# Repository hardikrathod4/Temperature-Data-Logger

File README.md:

# TEMPERATURE DATA LOGGER
8 channel K-type thermocouple temperature logger.

## FEATURES
* ESP32-WROOM-32E as a Controller
* 8 channel K-type thermocouple inputs (MAX31855KASA)
* 20x4 char LCD display
* MicroSD memory card interface
* Buzzer
* Power and data in/out over USB type-B connector
* RTC (PCF8563T)
* 4 buttons for menu
* 3 LEDs for status indication

## STATUS
### Hardware
- [X] In progress
- [ ] Completed
### Functional Testing (HW+SW)
- [ ] Programming
- [ ] Serial data over USB-B (Serial2)
- [ ] Menu Buttons check
- [ ] LEDs check
- [ ] RTC check
- [ ] LCD check
- [ ] Buzzer check
- [ ] microSD check
- [ ] Thermocouple temperature read check
- [ ] is somthing missing???
### Software
- [ ] TBD
### Enclosure
- [X] In progress
- [ ] Completed

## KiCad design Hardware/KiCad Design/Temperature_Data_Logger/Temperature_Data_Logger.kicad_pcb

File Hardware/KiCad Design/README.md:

# NOTE
It isn't recommended to use older version of the project.

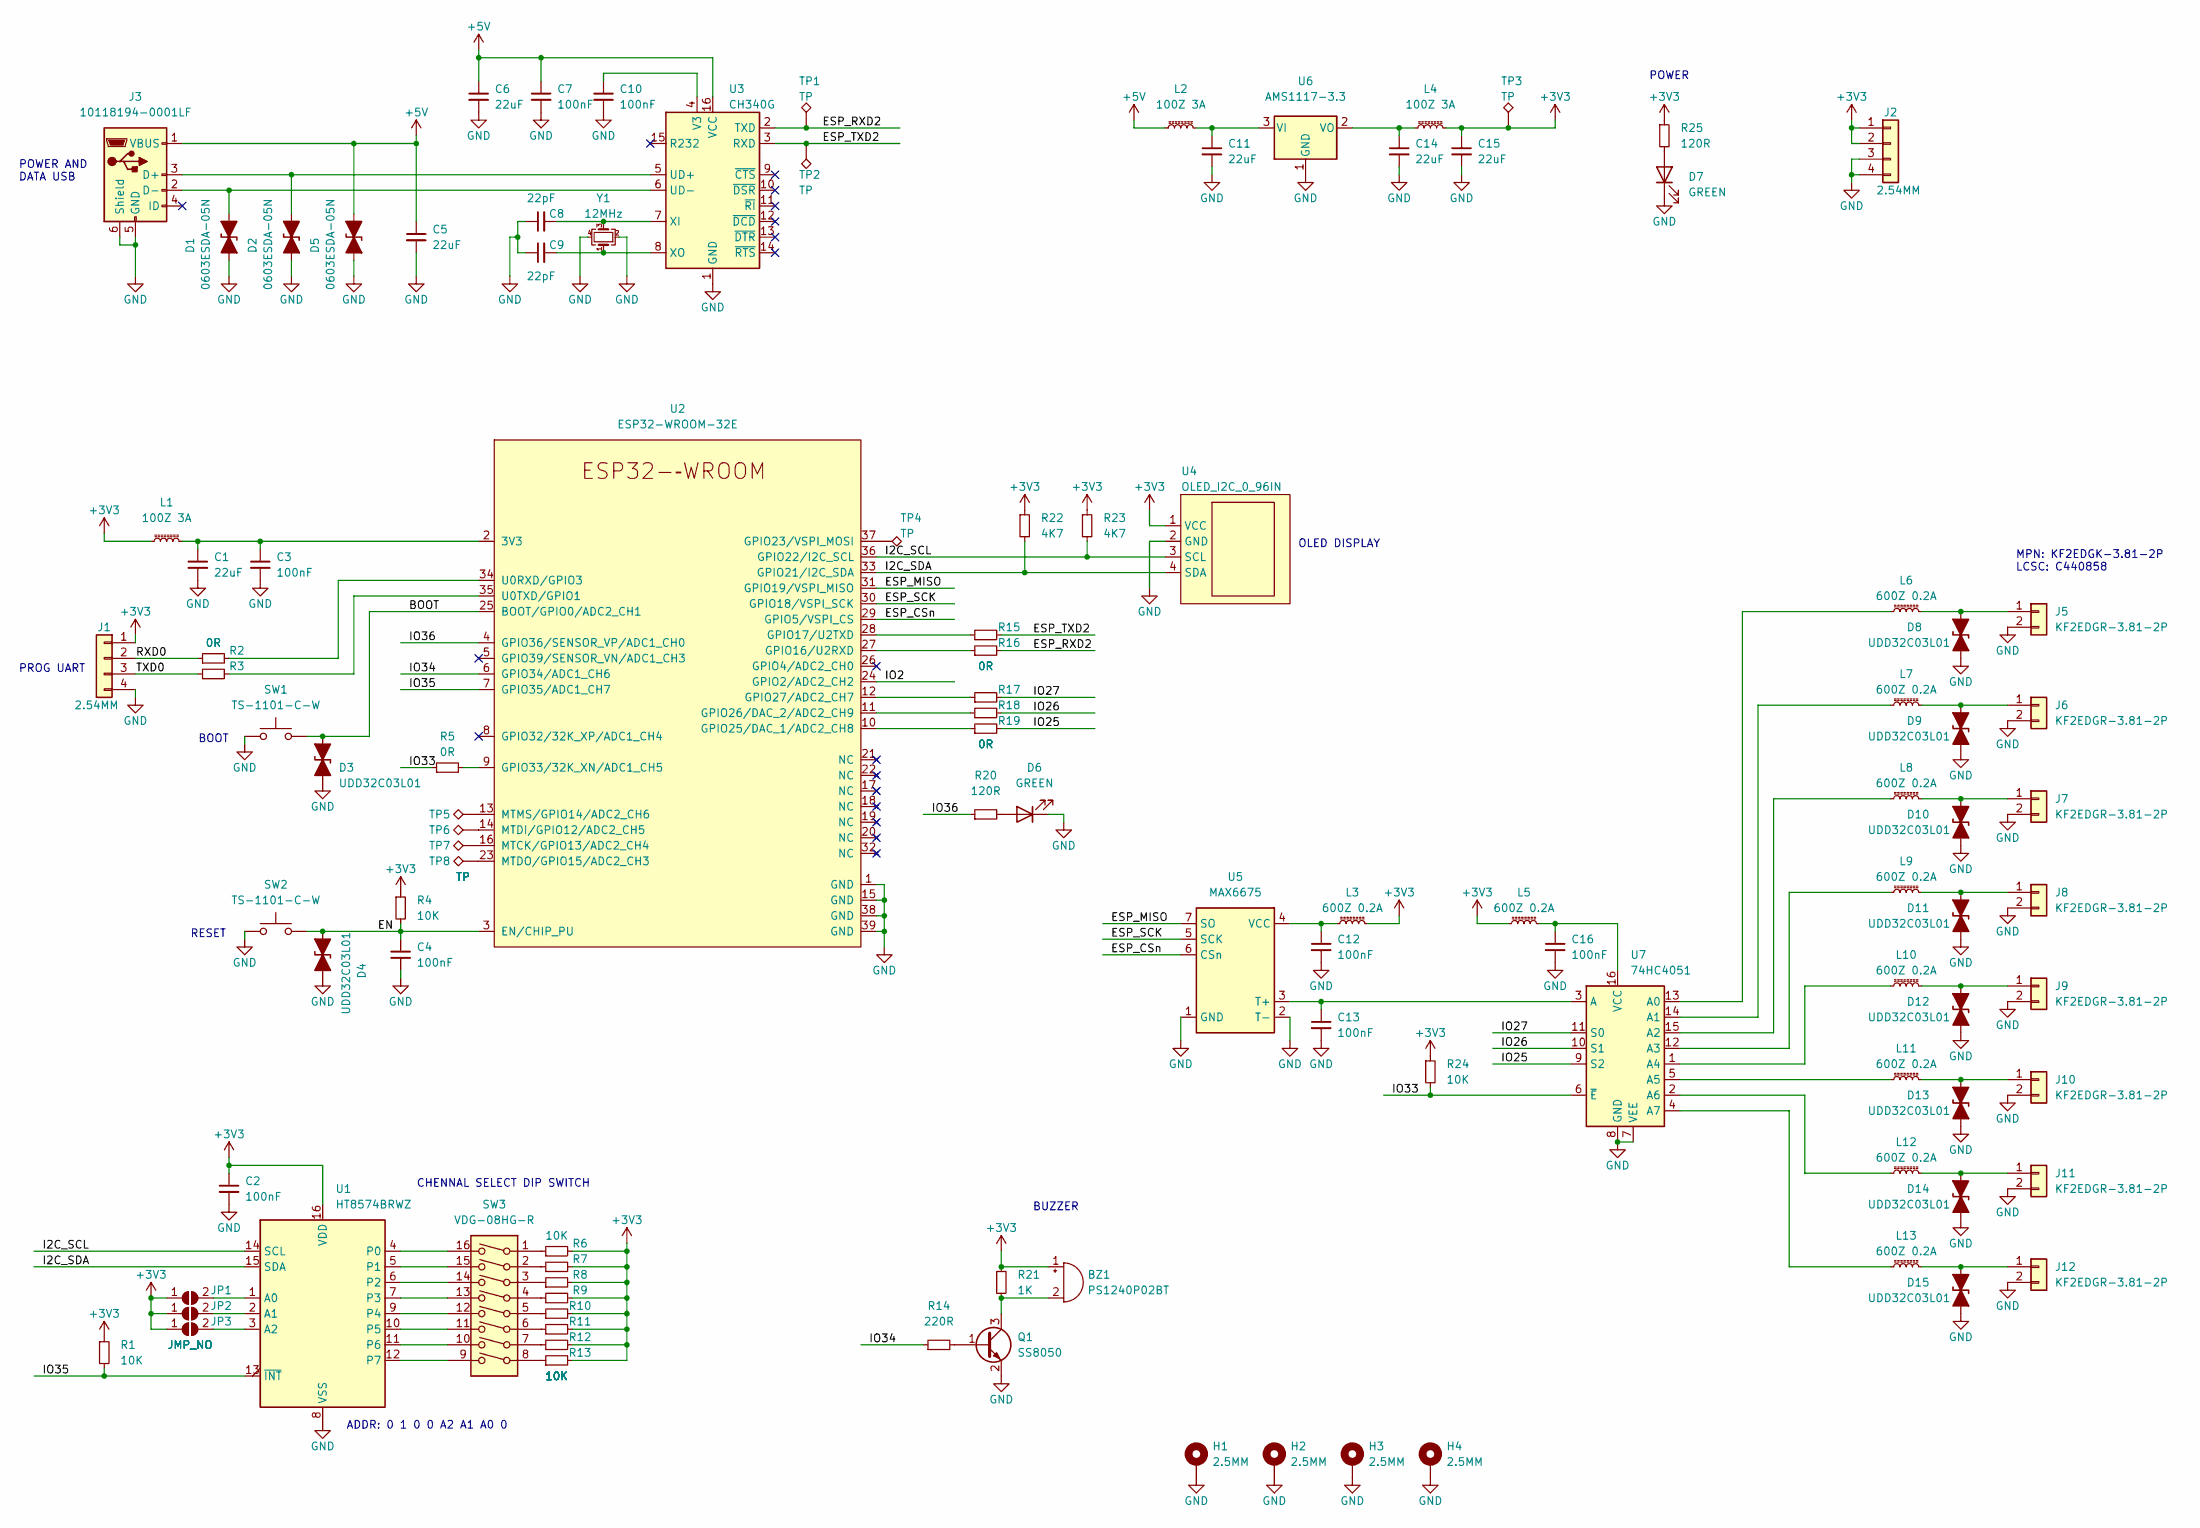
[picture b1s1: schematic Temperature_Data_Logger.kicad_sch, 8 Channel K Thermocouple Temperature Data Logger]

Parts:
BZ1: PS1240P02BT; Buzzer_TDK_PS1240P02BT_D12.2mm_H6.5mm; LCSC C76871
C1, C5, C6, C11, C14, C15: 22uF; C_0603_1608Metric; LCSC C59461
C2, C3, C4, C7, C10, C12, C13, C16: 100nF; C_0603_1608Metric; LCSC C14663
C8, C9: 22pF; C_0603_1608Metric; LCSC C1653
D1, D2, D5: 0603ESDA-05N; D_0603_1608Metric; LCSC C316054
D3, D4, D8, D9, D10, D11, D12, D13, D14, D15: UDD32C03L01; D_SOD-323_HandSoldering; LCSC C78439
D6, D7: GREEN; LED_D3.0mm_Clear; LCSC C559113
H1, H2, H3, H4: 2.5MM; MountingHole_2.7mm_M2.5_Pad_Via
J1, J2: 2.54MM; PinHeader_1x04_P2.54mm_Vertical; LCSC C358686
J3: 10118194-0001LF; USB_Micro-B_Amphenol_10118194_Horizontal; LCSC C132563
J5, J6, J7, J8, J9, J10, J11, J12: KF2EDGR-3.81-2P; PhoenixContact_MC_1,5_2-G-3.81_1x02_P3.81mm_Horizontal; LCSC C441182
JP1, JP2, JP3: JMP_NO; SolderJumper-2_P1.3mm_Open_RoundedPad1.0x1.5mm
L1, L2, L4: 100Z 3A; L_0603_1608Metric; LCSC C307769
L3, L5, L6, L7, L8, L9, L10, L11, L12, L13: 600Z 0.2A; L_0603_1608Metric; LCSC C1002
Q1: SS8050; SOT-23; LCSC C2150
R1, R4, R6, R7, R8, R9, R10, R11, R12, R13, R24: 10K; R_0603_1608Metric; LCSC C25804
R2, R3, R5, R15, R16, R17, R18, R19: 0R; R_0603_1608Metric; LCSC C21189
R14: 220R; R_0603_1608Metric; LCSC C22962
R20, R25: 120R; R_0603_1608Metric; LCSC C22787
R21: 1K; R_0603_1608Metric; LCSC C21190
R22, R23: 4K7; R_0603_1608Metric; LCSC C23162
SW1, SW2: TS-1101-C-W; SW_SPST_CK_RS282G05A3; LCSC C318938
SW3: VDG-08HG-R; SW_DIP_SPSTx08_Slide_9.78x22.5mm_W7.62mm_P2.54mm; LCSC C3663
TP1, TP2, TP3, TP4, TP5, TP6, TP7, TP8: TP; TestPoint_Pad_1.0x1.0mm
U1: HT8574BRWZ; SOIC-16W_7.5x10.3mm_P1.27mm; LCSC C2834482
U2: ESP32-WROOM-32E
U3: CH340G; SOIC-16_3.9x9.9mm_P1.27mm; LCSC C14267
U4: OLED_I2C_0_96IN; Display_128x64_096_I2C
U5: MAX6675; SOIC-8_5.23x5.23mm_P1.27mm; LCSC C16030
U6: AMS1117-3.3; SOT-223-3_TabPin2; LCSC C6186
U7: 74HC4051; SOIC-16_3.9x9.9mm_P1.27mm; LCSC C9386
Y1: 12MHz; Crystal_SMD_SeikoEpson_FA238V-4Pin_3.2x2.5mm; LCSC C9002

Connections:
+3V3: BZ1.1 (-), C2.1, C15.1, J1.1, J2.1, J2.2, JP1.1 (A), JP2.1 (A), JP3.1 (A), L1.1, L3.2, L4.2, L5.1, R1.1, R4.1, R6.2, R7.2, R8.2, R9.2, R10.2, R11.2, R12.2, R13.2, R21.1, R22.1, R23.1, R24.1, R25.1, TP3.1, U1.16 (VDD), U4.1 (VCC)
+5V: C5.1, C6.1, C7.1, D5.2 (A2), J3.1 (VBUS), L2.1, U3.16 (VCC)
/BOOT: D3.2 (A2), SW1.2, U2.25 (BOOT/GPIO0/ADC2_CH1)
/EN: C4.1, D4.2 (A2), R4.2, SW2.2, U2.3 (EN/CHIP_PU)
/ESP_CSn: U2.29 (GPIO5/VSPI_CS), U5.6 (CSn)
/ESP_MISO: U2.31 (GPIO19/VSPI_MISO), U5.7 (SO)
/ESP_RXD2: R16.2, TP1.1, U3.2 (TXD)
/ESP_SCK: U2.30 (GPIO18/VSPI_SCK), U5.5 (SCK)
/ESP_TXD2: R15.2, TP2.1, U3.3 (RXD)
/I2C_SCL: R23.2, U1.14 (SCL), U2.36 (GPIO22/I2C_SCL), U4.3 (SCL)
/I2C_SDA: R22.2, U1.15 (SDA), U2.33 (GPIO21/I2C_SDA), U4.4 (SDA)
/IO2: U2.24 (GPIO2/ADC2_CH2)
/IO25: R19.2, U7.9 (S2)
/IO26: R18.2, U7.10 (S1)
/IO27: R17.2, U7.11 (S0)
/IO33: R5.1, R24.2, U7.6 (~E)
/IO34: R14.1, U2.6 (GPIO34/ADC1_CH6)
/IO35: R1.2, U1.13 (~INT), U2.7 (GPIO35/ADC1_CH7)
/IO36: R20.1, U2.4 (GPIO36/SENSOR_VP/ADC1_CH0)
/RXD0: J1.2, R2.1
/TXD0: J1.3, R3.1
GND: C1.2, C2.2, C3.2, C4.2, C5.2, C6.2, C7.2, C8.1, C9.1, C10.2, C11.2, C12.2, C13.2, C14.2, C15.2, C16.2, D1.1 (A1), D2.1 (A1), D3.1 (A1), D4.1 (A1), D5.1 (A1), D6.1 (K), D7.1 (K), D8.1 (A1), D9.1 (A1), D10.1 (A1), D11.1 (A1), D12.1 (A1), D13.1 (A1), D14.1 (A1), D15.1 (A1), H1.1, H2.1, H3.1, H4.1, J1.4, J2.3, J2.4, J3.5 (GND), J3.6 (Shield), J5.2, J6.2, J7.2, J8.2, J9.2, J10.2, J11.2, J12.2, Q1.2 (E), SW1.1, SW2.1, U1.8 (VSS), U2.1 (GND), U2.15 (GND), U2.38 (GND), U2.39 (GND), U3.1 (GND), U4.2 (GND), U5.1 (GND), U5.2 (T-), U6.1 (GND), U7.7 (VEE), U7.8 (GND), Y1.2, Y1.4
unnamed: BZ1.2 (+), Q1.3 (C), R21.2
unnamed: C1.1, C3.1, L1.2, U2.2 (3V3)
unnamed: C8.2, U3.7 (XI), Y1.3
unnamed: C9.2, U3.8 (XO), Y1.1
unnamed: C10.1, U3.4 (V3)
unnamed: C11.1, L2.2, U6.3 (VI)
unnamed: C12.1, L3.1, U5.4 (VCC)
unnamed: C13.1, U5.3 (T+), U7.3 (A)
unnamed: C14.1, L4.1, U6.2 (VO)
unnamed: C16.1, L5.2, U7.16 (VCC)
unnamed: D1.2 (A2), J3.2 (D-), U3.6 (UD-)
unnamed: D2.2 (A2), J3.3 (D+), U3.5 (UD+)
unnamed: D6.2 (A), R20.2
unnamed: D7.2 (A), R25.2
unnamed: D8.2 (A2), J5.1, L6.2
unnamed: D9.2 (A2), J6.1, L7.2
unnamed: D10.2 (A2), J7.1, L8.2
unnamed: D11.2 (A2), J8.1, L9.2
unnamed: D12.2 (A2), J9.1, L10.2
unnamed: D13.2 (A2), J10.1, L11.2
unnamed: D14.2 (A2), J11.1, L12.2
unnamed: D15.2 (A2), J12.1, L13.2
unnamed: JP1.2 (B), U1.1 (A0)
unnamed: JP2.2 (B), U1.2 (A1)
unnamed: JP3.2 (B), U1.3 (A2)
unnamed: L6.1, U7.13 (A0)
unnamed: L7.1, U7.14 (A1)
unnamed: L8.1, U7.15 (A2)
unnamed: L9.1, U7.12 (A3)
unnamed: L10.1, U7.1 (A4)
unnamed: L11.1, U7.5 (A5)
unnamed: L12.1, U7.2 (A6)
unnamed: L13.1, U7.4 (A7)
unnamed: Q1.1 (B), R14.2
unnamed: R2.2, U2.34 (U0RXD/GPIO3)
unnamed: R3.2, U2.35 (U0TXD/GPIO1)
unnamed: R5.2, U2.9 (GPIO33/32K_XN/ADC1_CH5)
unnamed: R6.1, SW3.1
unnamed: R7.1, SW3.2
unnamed: R8.1, SW3.3
unnamed: R9.1, SW3.4
unnamed: R10.1, SW3.5
unnamed: R11.1, SW3.6
unnamed: R12.1, SW3.7
unnamed: R13.1, SW3.8
unnamed: R15.1, U2.28 (GPIO17/U2TXD)
unnamed: R16.1, U2.27 (GPIO16/U2RXD)
unnamed: R17.1, U2.12 (GPIO27/ADC2_CH7)
unnamed: R18.1, U2.11 (GPIO26/DAC_2/ADC2_CH9)
unnamed: R19.1, U2.10 (GPIO25/DAC_1/ADC2_CH8)
unnamed: SW3.9, U1.12 (P7)
unnamed: SW3.10, U1.11 (P6)
unnamed: SW3.11, U1.10 (P5)
unnamed: SW3.12, U1.9 (P4)
unnamed: SW3.13, U1.7 (P3)
unnamed: SW3.14, U1.6 (P2)
unnamed: SW3.15, U1.5 (P1)
unnamed: SW3.16, U1.4 (P0)
unnamed: TP4.1, U2.37 (GPIO23/VSPI_MOSI)
unnamed: TP5.1, U2.13 (MTMS/GPIO14/ADC2_CH6)
unnamed: TP6.1, U2.14 (MTDI/GPIO12/ADC2_CH5)
unnamed: TP7.1, U2.16 (MTCK/GPIO13/ADC2_CH4)
unnamed: TP8.1, U2.23 (MTDO/GPIO15/ADC2_CH3)

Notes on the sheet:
BUZZER
OLED DISPLAY
ADDR: 0 1 0 0 A2 A1 A0 0
CHENNAL SELECT DIP SWITCH
MPN: KF2EDGK-3.81-2P LCSC: C440858
RESET
POWER
POWER AND DATA USB
BOOT
PROG UART

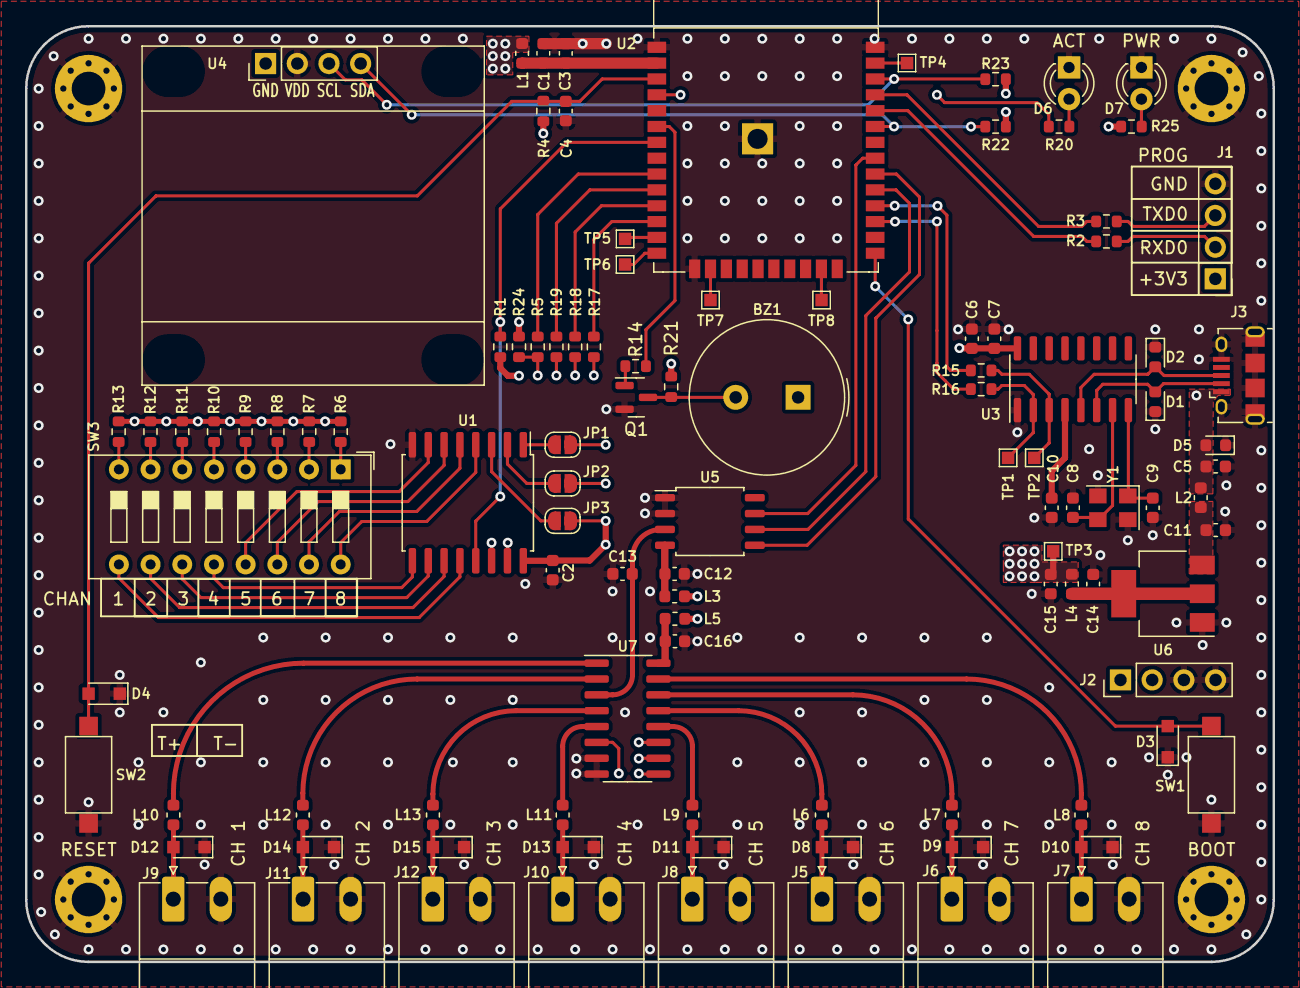
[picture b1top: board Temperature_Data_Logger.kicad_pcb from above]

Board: 4 copper layers, 100.0 x 75.0 mm, 108 parts (0 on the bottom side), 84 nets.

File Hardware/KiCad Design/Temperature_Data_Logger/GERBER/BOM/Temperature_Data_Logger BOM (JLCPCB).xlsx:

Comment | Designator | Footprint | JLCPCB Part
PS1240P02BT | BZ1 | Buzzer_Beeper:Buzzer_TDK_PS1240P02BT_D12.2mm_H6.5mm | C76871
22uF | C1, C5, C6, C11, C14, C15 | Capacitor_SMD:C_0603_1608Metric | C59461
100nF | C2, C3, C4, C7, C10, C12, C13, C16 | Capacitor_SMD:C_0603_1608Metric | C14663
22pF | C8, C9 | Capacitor_SMD:C_0603_1608Metric | C1653
0603ESDA-05N | D1, D2, D5 | Diode_SMD:D_0603_1608Metric | C316054
UDD32C03L01 | D3, D4, D8, D9, D10, D11, D12, D13, D14, D15 | Diode_SMD:D_SOD-323_HandSoldering | C78439
GREEN | D6, D7 | LED_THT:LED_D3.0mm_Clear | C559113
2.5MM | H1, H2, H3, H4 | MountingHole:MountingHole_2.7mm_M2.5_Pad_Via
2.54MM | J1, J2 | Connector_PinHeader_2.54mm:PinHeader_1x04_P2.54mm_Vertical | C358686
10118194-0001LF | J3 | Temperature Data Logger:USB_Micro-B_Amphenol_10118194_Horizontal | C132563
KF2EDGR-3.81-2P | J5, J6, J7, J8, J9, J10, J11, J12 | Connector_Phoenix_MC:PhoenixContact_MC_1,5_2-G-3.81_1x02_P3.81mm_Horizontal | C441182
JMP_NO | JP1, JP2, JP3 | Jumper:SolderJumper-2_P1.3mm_Open_RoundedPad1.0x1.5mm
100Z 3A | L1, L2, L4 | Inductor_SMD:L_0603_1608Metric | C307769
600Z 0.2A | L3, L5, L6, L7, L8, L9, L10, L11, L12, L13 | Inductor_SMD:L_0603_1608Metric | C1002
SS8050 | Q1 | Package_TO_SOT_SMD:SOT-23 | C2150
10K | R1, R4, R6, R7, R8, R9, R10, R11, R12, R13, R24 | Resistor_SMD:R_0603_1608Metric | C25804
0R | R2, R3, R5, R15, R16, R17, R18, R19 | Resistor_SMD:R_0603_1608Metric | C21189
220R | R14 | Resistor_SMD:R_0603_1608Metric | C22962
120R | R20, R25 | Resistor_SMD:R_0603_1608Metric | C22787
1K | R21 | Resistor_SMD:R_0603_1608Metric | C21190
4K7 | R22, R23 | Resistor_SMD:R_0603_1608Metric | C23162
TS-1101-C-W | SW1, SW2 | Button_Switch_SMD:SW_SPST_CK_RS282G05A3 | C318938
VDG-08HG-R | SW3 | Button_Switch_THT:SW_DIP_SPSTx08_Slide_9.78x22.5mm_W7.62mm_P2.54mm | C3663
TP | TP1, TP2, TP3, TP4, TP5, TP6, TP7, TP8 | TestPoint:TestPoint_Pad_1.0x1.0mm
HT8574BRWZ | U1 | Package_SO:SOIC-16W_7.5x10.3mm_P1.27mm | C2834482
ESP32-WROOM-32E | U2 | Temperature Data Logger:ESP32-WROOM-32E
CH340G | U3 | Package_SO:SOIC-16_3.9x9.9mm_P1.27mm | C14267
OLED_I2C_0_96IN | U4 | Temperature Data Logger:Display_128x64_096_I2C
MAX6675 | U5 | Temperature Data Logger:SOIC-8_5.23x5.23mm_P1.27mm | C16030
AMS1117-3.3 | U6 | Package_TO_SOT_SMD:SOT-223-3_TabPin2 | C6186
74HC4051 | U7 | Package_SO:SOIC-16_3.9x9.9mm_P1.27mm | C9386
12MHz | Y1 | Crystal:Crystal_SMD_SeikoEpson_FA238V-4Pin_3.2x2.5mm | C9002

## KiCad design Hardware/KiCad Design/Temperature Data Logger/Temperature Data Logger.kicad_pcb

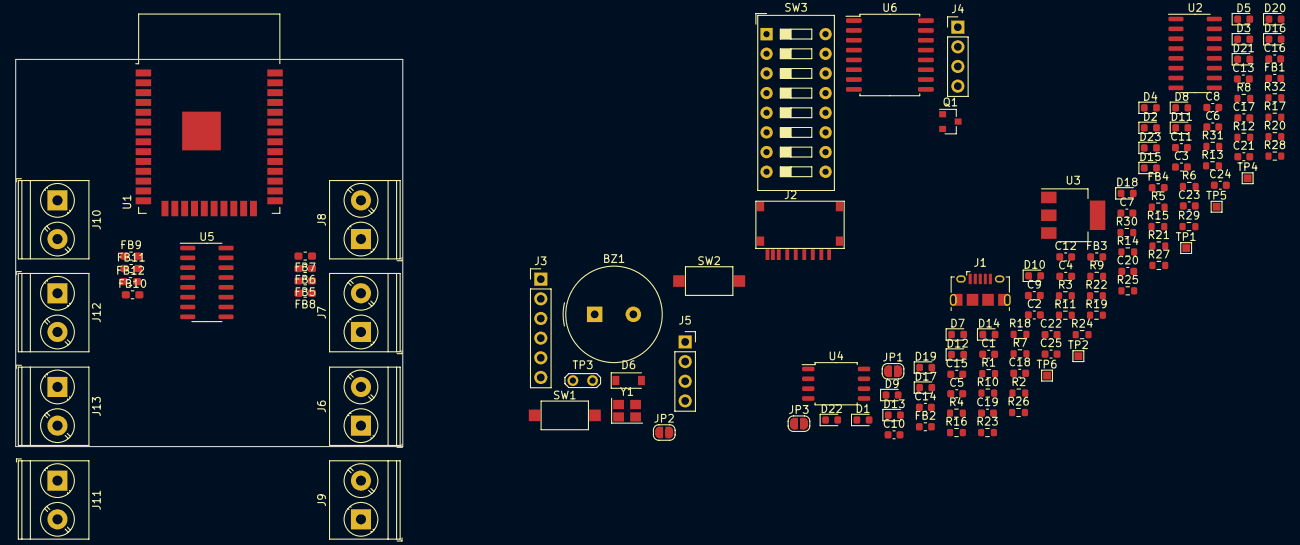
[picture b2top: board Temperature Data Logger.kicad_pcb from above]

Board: 2 copper layers, 50.0 x 50.0 mm, 126 parts (0 on the bottom side), 95 nets, no tracks yet.

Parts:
BZ1: PS1240P02BT; Buzzer_TDK_PS1240P02BT_D12.2mm_H6.5mm
C1, C4, C6, C11, C12, C13, C16: 22uF; C_0603_1608Metric
C2: 1uF; C_0603_1608Metric
C3, C5, C7, C10, C14, C15, C17: 100nF; C_0603_1608Metric
C8, C9: 22pF; C_0603_1608Metric
C18, C19, C20, C21, C22, C23, C24, C25: 10nF; C_0603_1608Metric
D1, D2, D7, D8, D9, D10, D12, D13, D14, D16, D17, D18, D19, D20, D21, D22, D23: UDD32C03L01; D_0603_1608Metric
D3, D4, D5: 0603ESDA-05N; D_0603_1608Metric
D6: B5819W SL; D_SOD-123
D11, D15: Yellow; LED_0603_1608Metric
FB1, FB2, FB3, FB4: 100Z 3A; L_0603_1608Metric
FB5, FB6, FB7, FB8, FB9, FB10, FB11, FB12: 600Z 0.2A; L_0603_1608Metric_Pad1.05x0.95mm_HandSolder
J1: 10118194-0001LF; USB_Micro-B_Amphenol_10118194_Horizontal
J2: TF-018; microSD_TF-018
J3: 2.54MM; PinHeader_1x06_P2.54mm_Vertical
J4: 2.54MM; PinHeader_1x04_P2.54mm_Vertical
J5: Conn_01x04; PinSocket_1x04_P2.54mm_Vertical
J6, J7, J8, J9, J10, J11, J12, J13: XY300V-A-5.0-2P; TerminalBlock_Phoenix_PT-1,5-2-5.0-H_1x02_P5.00mm_Horizontal
JP1, JP2, JP3: JMP_NC; SolderJumper-2_P1.3mm_Open_RoundedPad1.0x1.5mm
Q1: SS8050; SOT-23
R1, R21, R24, R25, R26, R27, R28, R29, R30, R31, R32: 10K; R_0603_1608Metric
R2, R3, R5, R6, R7, R8, R9, R10, R11, R12, R13, R14, R15, R16, R17: 0R; R_0603_1608Metric
R4, R23: 750R; R_0603_1608Metric
R18, R19: 4K7; R_0603_1608Metric
R20: 220R; R_0603_1608Metric
R22: 1K; R_0603_1608Metric
SW1, SW2: TS-1101-C-W; SW_SPST_CK_RS282G05A3
SW3: VDG-08HG-R; SW_DIP_SPSTx08_Slide_9.78x22.5mm_W7.62mm_P2.54mm
TP1, TP2, TP4, TP5, TP6: TP; TestPoint_Pad_1.0x1.0mm
TP3: TP_2Pole; TestPoint_2Pads_Pitch2.54mm_Drill0.8mm
U1: ESP32-WROOM-32E; ESP32-WROOM-32
U2: CH340G; SOIC-16_3.9x9.9mm_P1.27mm
U3: AMS1117-3.3; SOT-223-3_TabPin2
U4: MAX6675; SOIC-8_5.23x5.23mm_P1.27mm
U5: 74HC4051; SOIC-16_3.9x9.9mm_P1.27mm
U6: HT8574BRWZ; SOIC-16W_7.5x10.3mm_P1.27mm
Y1: 12MHz; Crystal_SMD_SeikoEpson_FA238-4Pin_3.2x2.5mm

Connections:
+3V3: BZ1.1, C5.1, C13.1, C15.1, C16.1, C17.1, FB1.2, FB3.1, FB4.1, J2.4, J3.1, J4.1, J5.1, JP1.1, JP2.1, JP3.1, R1.1, R18.1, R19.1, R21.1, R22.1, R23.2, R24.1, R25.1, R26.1, R27.1, R28.1, R29.1, R30.1, R31.1, R32.1, TP3.1, U5.16, U6.16
+5V: C4.1, C6.1, C7.1, D6.1, FB2.2, U2.16
/BOOT: D1.2, SW1.2, U1.25
/EN: C2.1, D2.2, R1.2, SW2.2, U1.3
/ESP_CSn: U1.29, U4.6
/ESP_MISO: U1.31, U4.7
/ESP_RXD2: R13.1, TP1.1, U2.2
/ESP_SCK: U1.30, U4.5
/ESP_TXD2: R12.1, TP2.1, U2.3
/I2C_SCL: J5.3, R19.2, U1.36, U6.14
/I2C_SDA: J5.4, R18.2, U1.33, U6.15
/IO25: R16.1, U5.9
/IO26: R15.1, U5.10
/IO27: R14.1, U5.11
/IO33: R17.1, R21.2, U5.6
/IO_EXP_INTn: R24.2, U6.13
/MMC_CLK: J3.2, R8.2, U1.13
/MMC_CMD: J3.5, R7.2, U1.23
/MMC_DAT0: R9.2, U1.24
/MMC_DAT1: R10.2, U1.26
/MMC_DAT2: J3.3, R5.2, U1.14
/MMC_DAT3: J3.4, R6.2, U1.16
/MMC_DET: R11.2, U1.12
/RXD0: J4.2, R2.2
/TXD0: J4.3, R3.2
GND: C1.2, C2.2, C3.2, C4.2, C5.2, C6.2, C7.2, C8.2, C9.2, C10.2, C11.2, C12.2, C13.2, C14.2, C15.2, C16.2, C17.2, C18.2, C19.2, C20.2, C21.2, C22.2, C23.2, C24.2, C25.2, D1.1, D2.1, D3.2, D4.2, D5.2, D7.1, D8.1, D9.1, D10.1, D11.1, D12.1, D13.1, D14.1, D15.1, D16.2, D17.2, D18.2, D19.2, D20.2, D21.2, D22.2, D23.2, J1.5, J1.6, J2.6, J2.10, J3.6, J4.4, J5.2, J6.2, J7.2, J8.2, J9.2, J10.2, J11.2, J12.2, J13.2, Q1.2, SW1.1, SW2.1, TP3.2, U1.1, U1.15, U1.38, U1.39, U2.1, U3.1, U4.1, U4.2, U5.7, U5.8, U6.8, Y1.2, Y1.4
unnamed: BZ1.2, Q1.3, R22.2
unnamed: C1.1, C3.1, FB1.1, U1.2
unnamed: C8.1, U2.7, Y1.1
unnamed: C9.1, U2.8, Y1.3
unnamed: C10.1, U2.4
unnamed: C11.1, FB2.1, U3.3
unnamed: C12.1, FB3.2, U3.2
unnamed: C14.1, FB4.2, U4.4
unnamed: C18.1, FB5.2, U5.13
unnamed: C19.1, FB6.2, U5.14
unnamed: C20.1, FB7.2, U5.15
unnamed: C21.1, FB8.2, U5.12
unnamed: C22.1, FB9.2, U5.1
unnamed: C23.1, FB10.2, U5.5
unnamed: C24.1, FB11.2, U5.2
unnamed: C25.1, FB12.2, U5.4
unnamed: D3.1, J1.2, U2.6
unnamed: D4.1, J1.3, U2.5
unnamed: D5.1, D6.2, J1.1
unnamed: D7.2, J2.9, R11.1
unnamed: D8.2, J2.8, R10.1
unnamed: D9.2, J2.7, R9.1
unnamed: D10.2, J2.5, R8.1
unnamed: D11.2, R4.1
unnamed: D12.2, J2.3, R7.1
unnamed: D13.2, J2.2, R6.1
unnamed: D14.2, J2.1, R5.1
unnamed: D15.2, R23.1
unnamed: D16.1, FB5.1, J6.1
unnamed: D17.1, FB6.1, J7.1
unnamed: D18.1, FB7.1, J8.1
unnamed: D19.1, FB8.1, J9.1
unnamed: D20.1, FB9.1, J10.1
unnamed: D21.1, FB10.1, J11.1
unnamed: D22.1, FB11.1, J12.1
unnamed: D23.1, FB12.1, J13.1
unnamed: JP1.2, U6.1
unnamed: JP2.2, U6.2
unnamed: JP3.2, U6.3
unnamed: Q1.1, R20.1
unnamed: R2.1, U1.34
unnamed: R3.1, U1.35
unnamed: R4.2, U1.4
unnamed: R12.2, U1.28
unnamed: R13.2, U1.27
unnamed: R14.2, U1.11
unnamed: R15.2, U1.10
unnamed: R16.2, U1.9
unnamed: R17.2, U1.8
unnamed: R25.2, SW3.16
unnamed: R26.2, SW3.15
unnamed: R27.2, SW3.14
unnamed: R28.2, SW3.13
unnamed: R29.2, SW3.12
unnamed: R30.2, SW3.11
unnamed: R31.2, SW3.10
unnamed: R32.2, SW3.9
unnamed: SW3.1, U6.4
unnamed: SW3.2, U6.5
unnamed: SW3.3, U6.6
unnamed: SW3.4, U6.7
unnamed: SW3.5, U6.9
unnamed: SW3.6, U6.10
unnamed: SW3.7, U6.11
unnamed: SW3.8, U6.12
unnamed: TP4.1, U1.7
unnamed: TP5.1, U1.6
unnamed: TP6.1, U1.5
unnamed: U4.3, U5.3

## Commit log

2021-12-12 Create .gitkeep
    Contains hardware specific files
2021-12-12 Rename Readme.md to README.md
2021-12-12 Add files via upload
    Thermocouple to Digital Converter
2021-12-12 Create DS-16278-CH340E.pdf
    datasheet TTL to USB
2021-12-12 Create DS18B20.pdf
    datasheet temperature sensor
2021-12-15 added: esp32-s2-wroom-1 in schematic lib
2021-12-28 chaneg: ESP32-S3 to ESP32
2021-12-30 removed KiCad 5 project
2022-01-05 initial version
2022-01-06 added PCB docs
2022-01-06 Renamed
2022-01-06 added 3D view picture
2022-01-07 formatting
2022-01-09 updated PCB 3D model
2022-01-29 added IO expander datasheet
2022-02-20 remove docs
2022-02-20 added MAX31855 datasheet
2022-03-13 added: interactive html BOM
2022-04-12 LCD circuit correction
2022-04-24 added microSD
2022-04-24 removed old Gerber data
2022-04-24 added updated Gerber data
2022-12-31 added: menu buttons, RTC, 8 channels, USB-B, microSD and LEDs
2022-12-31 added: pcb pdf
2023-01-02 added: 20x4 Char LCD display datasheet

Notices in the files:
Hardware/KiCad Design/Temperature_Data_Logger/Temperature_Data_Logger.kicad_pcb:
OPENSOURCE (MIT License)
